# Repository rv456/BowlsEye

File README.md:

# Bowls Eye
-----------

Repository for team 18's Real Time Embedded Programming Raspberry Pi project.

Watch our promotional video at the link below!

# Installation
----------------

To install the bowls eye system on the Raspberry Pi run the following

    git clone https://github.com/rv456/BowlsEye.git
    cd BowlsEye/Code/Pi_BowlsEyeMain/
    make
    ./main
    
## Dependancies

The BowlsEye system requies Bluez and pigpio libraries.  It also requires that SPI and bluethooth are enabled on the Raspberry Pi

### Bluetooth 
    sudo apt-get install bluetooth blueman bluez libbluetooth-dev

### PIGPIO

    rm pigpio.tar
    sudo rm -rf PIGPIO
    wget abyz.me.uk/rpi/pigpio/pigpio.tar
    tar xf pigpio.tar
    cd PIGPIO
    make
    sudo make install
    
from the installation instructions [here](http://abyz.me.uk/rpi/pigpio/download.html)

### SPI

    sudo raspi-config

navigate to SPI and enable, you will then need to reboot the Pi to enable the changes

    sudo reboot

---------------------

## Repository Structure

[Code](https://github.com/rv456/BowlsEye/tree/master/Code) contains all of the code written for the Raspberry Pi and the external GUI.  Code documentation can be found [here](https://rv456.github.io/BowlsEye/).

[KiCad](https://github.com/rv456/BowlsEye/tree/master/KiCad) contains the various hardware design files used throught the project, including a full [BOM](https://github.com/rv456/BowlsEye/blob/master/KiCad/Shield/Fabrication/BOM/BOMfull.csv) and fabrication files. (note that part numbers for everything used in the project can also be found directly in the [schematics](https://github.com/rv456/BowlsEye/blob/master/KiCad/Shield) thanks to [kifields](http://kifield.readthedocs.io/en/latest/).

[Planner](https://github.com/rv456/BowlsEye/tree/master/Planner) contains documents related to project planning.  These will be removed once the project is completed.

[Resources](https://github.com/rv456/BowlsEye/tree/master/Resources) contains various datasheets, notes and other supporting files.

-----------

## Team Structure

[Harvey Leicester](https://github.com/rv456): Raspberry Pi programming and hardware design.

[Calum West](https://github.com/CalumWest): GUI programming and ultrasound guru.

# Problem
----------

Assistive technology is used throughout many sports to aid referees to determine the correct decision, or allow competitors to appeal against said decisions.  However, in the sport of lawn bowls, there is still a large factor of human error that can occur when measuring the distance between the jack and the bowls when the game is close.  As this is currently done with standard measurement techniques, any misreading of this distance by the referee will determine the wrong outcome of the game.  Therefore, this project aims to remove the possibility of human error in these measurements by designing a real time embedded system that can perform these measurments more accurately than a human.

# Solution
-----------

We have designed a system which uses ultrasonic transducers mounted on a stepper motor in order to map the distance from the jack to the surrounding area. This data is read via SPI by a Raspberry Pi and then transmitted via Bluetooth for a display on a GUI. More information can be found on our [wiki](https://github.com/rv456/BowlsEye/wiki).

A system overview is shown below, and you can follow our progress via this git, or our [facebook](https://www.facebook.com/Bowls-Eye-102409543919161/) or [twitter](https://twitter.com/bowlseyepi).

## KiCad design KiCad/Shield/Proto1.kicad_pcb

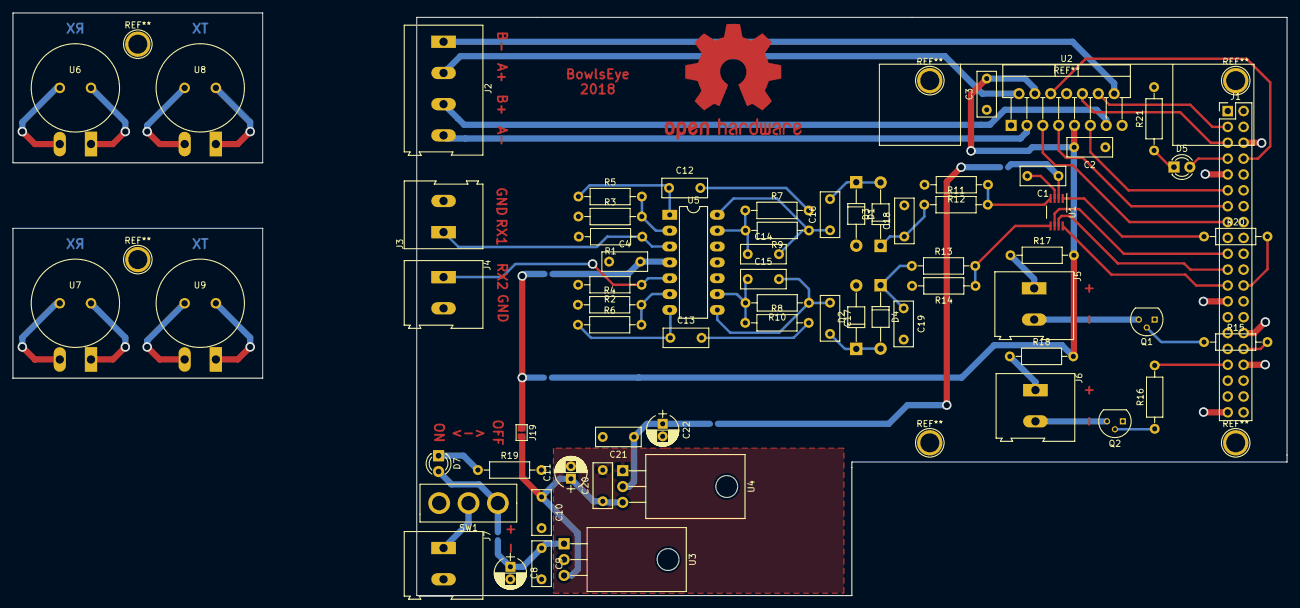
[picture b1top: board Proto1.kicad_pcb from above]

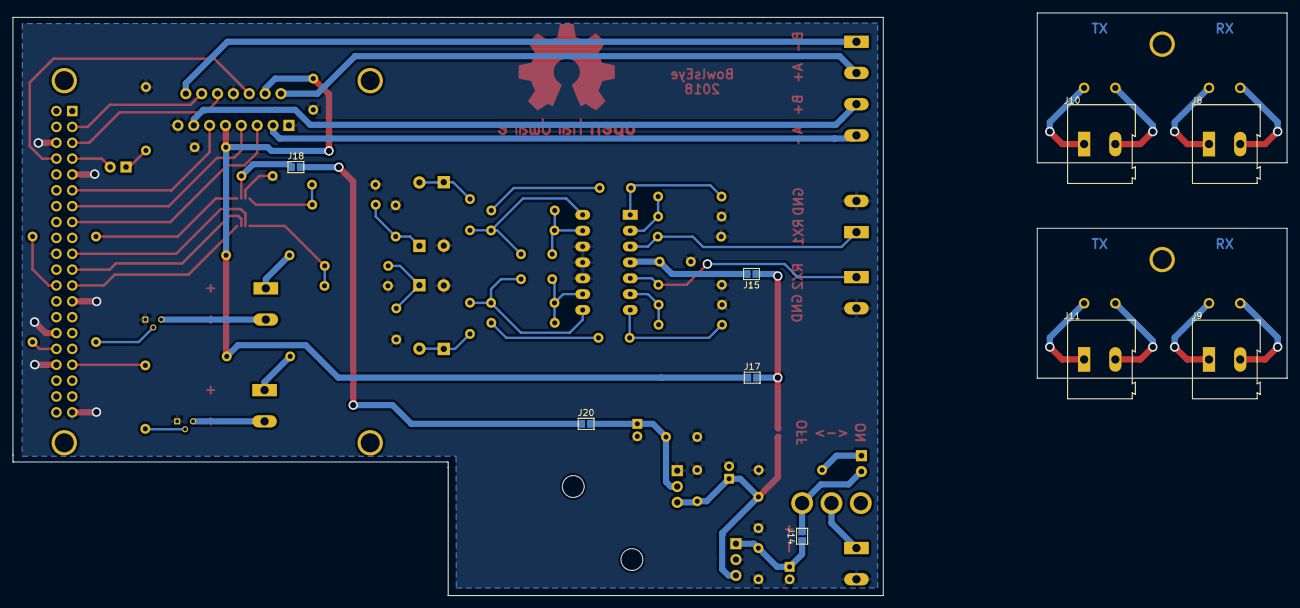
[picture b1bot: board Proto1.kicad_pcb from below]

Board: 2 copper layers, 204.1 x 93.3 mm, 75 parts (9 on the bottom side), 52 nets.

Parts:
C1, C2, C3, C4, C9, C10, C20, C21: 100nF; C_Rect_L7.2mm_W3.0mm_P5.00mm_FKS2_FKP2_MKS2_MKP2
C8, C11, C22: 10uF; CP_Radial_D5.0mm_P2.00mm
C12, C13: 10nF; C_Rect_L7.2mm_W3.0mm_P5.00mm_FKS2_FKP2_MKS2_MKP2
C14, C15: 10pF; C_Rect_L7.2mm_W3.0mm_P5.00mm_FKS2_FKP2_MKS2_MKP2
C16, C17, C18, C19: 1nF; C_Rect_L7.2mm_W3.0mm_P5.00mm_FKS2_FKP2_MKS2_MKP2
D1, D2, D3, D4: D; D_T-1_P10.16mm_Horizontal
D5, D7: LED; LED_D3.0mm
J1: CONN_02X20; Pin_Header_Straight_2x20_Pitch2.54mm
J2: CONN_01X04; TerminalBlock_Altech_AK300-4_P5.00mm
J3, J4, J5, J6, J7, J8, J9, J10, J11: CONN_01X02; TerminalBlock_Altech_AK300-2_P5.00mm
J14, J15, J17, J18, J19, J20: GS2
Q1, Q2: 2N3904; TO-92_Molded_Narrow
R1, R2: 3K9; R_Axial_DIN0207_L6.3mm_D2.5mm_P10.16mm_Horizontal
R3, R4, R7, R8: 1K; R_Axial_DIN0207_L6.3mm_D2.5mm_P10.16mm_Horizontal
R5, R6, R9, R10: 100K; R_Axial_DIN0207_L6.3mm_D2.5mm_P10.16mm_Horizontal
R11, R12, R13, R14, R15, R16, R17, R18, R19, R21: R; R_Axial_DIN0207_L6.3mm_D2.5mm_P10.16mm_Horizontal
R20: 0R; R_Axial_DIN0207_L6.3mm_D2.5mm_P10.16mm_Horizontal
SW1: SW_SPDT; SPDT
U1: ADC122S101; MyVSSOP-8_3.0x3.0mm_Pitch0.65mm
U2: L298_TH; TO-220-15_Vertical_StaggeredType1
U3: L78S05CV; TO-220-3_Horizontal
U4: LD1117S33TR_SOT223; TO-220-3_Horizontal
U5: LM324N; DIP-14_W7.62mm_LongPads
U6, U7, U8, U9: transducer

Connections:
+3V3: C1.1, C21.1, C22.1, J18.1, J18.2, J20.1, J20.2, U1.2, U4.2
+5V: C2.2, C3.2, C4.2, C10.1, C11.1, C20.1, J15.1, J15.2, J17.1, J17.2, J19.1, J19.2, R17.2, R18.2, U2.4, U2.9, U3.3, U4.3, U5.4
+Vs: C8.1, C9.1, D7.2, J14.1, J14.2, SW1.3, U3.1
DEBUG_PIN: D5.2, J1.7
GNDD: C1.2, C2.1, C3.1, C4.1, C8.2, C9.2, C10.2, C11.2, C18.2, C19.2, C20.2, C21.2, C22.2, D1.2, D2.2, J1.6, J1.9, J1.20, J1.25, J1.30, J1.34, J1.39, J3.2, J4.2, J7.2, J8.2, J9.2, Q1.1, Q2.1, R1.2, R2.2, R3.1, R4.1, R12.2, R14.2, R19.2, R21.2, U1.3, U2.1, U2.8, U2.15, U3.2, U4.1, U5.10, U5.11, U5.12, U6.2, U7.2
MOTOR_1_1: J1.15, U2.5
MOTOR_1_2: J1.13, U2.7
MOTOR_2_1: J1.5, U2.10
MOTOR_2_2: J1.3, U2.12
MOTOR_ENA: J1.8, U2.6
MOTOR_ENB: J1.11, U2.11
unnamed: C12.1, R5.1, U5.1
unnamed: C12.2, R7.2
unnamed: C13.1, R6.1, U5.7
unnamed: C13.2, R8.2
unnamed: C14.1, R7.1, R9.2, U5.13
unnamed: C14.2, C16.1, R9.1, U5.14
unnamed: C15.1, R8.1, R10.2, U5.9
unnamed: C15.2, C17.1, R10.1, U5.8
unnamed: C16.2, D1.1, D3.2
unnamed: C17.2, D2.1, D4.2
unnamed: C18.1, D3.1, R11.1
unnamed: C19.1, D4.1, R13.1
unnamed: D5.1, R21.1
unnamed: D7.1, R19.1
unnamed: J5.1, R17.1
unnamed: J5.2, Q1.3
unnamed: J6.1, R18.1
unnamed: J6.2, Q2.3
unnamed: J7.1, SW1.2
unnamed: J10.1, U8.1
unnamed: J10.2, U8.2
unnamed: J11.1, U9.1
unnamed: J11.2, U9.2
unnamed: Q1.2, R15.1
unnamed: Q2.2, R16.1
unnamed: R3.2, R5.2, U5.2
unnamed: R4.2, R6.2, U5.6
PHASE_A: J2.2, U2.2
PHASE_A-: J2.4, U2.3
PHASE_B: J2.3, U2.13
PHASE_B-: J2.1, U2.14
SPI_MISO: J1.21, U1.7
SPI_MOSI: J1.19, U1.6
SPI_NSS0: J1.24, R20.1, R20.2, U1.1
SPI_SCK: J1.23, U1.8
ULTRA_RX1: R11.2, R12.1, U1.4
ULTRA_RX1_RAW: J3.1, J8.1, R1.1, U5.3, U6.1
ULTRA_RX2: R13.2, R14.1, U1.5
ULTRA_RX2_RAW: J4.1, J9.1, R2.1, U5.5, U7.1
ULTRA_TX1: J1.32, R15.2
ULTRA_TX2: J1.33, R16.2

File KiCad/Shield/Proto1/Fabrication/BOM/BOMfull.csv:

Reference, Quantity, Value, Footprint, Datasheet, part#, rs#
C10 C20 C21 ,3,100nF,Capacitors_THT:C_Rect_L7.2mm_W3.0mm_P5.00mm_FKS2_FKP2_MKS2_MKP2,,,
C11 C22 ,2,10uF,Capacitors_THT:CP_Radial_D5.0mm_P2.00mm,,,
C12 C13 ,2,10nF,Capacitors_THT:C_Rect_L7.2mm_W3.0mm_P5.00mm_FKS2_FKP2_MKS2_MKP2,,UofG,
C14 C15 ,2,10pF,Capacitors_THT:C_Rect_L7.2mm_W3.0mm_P5.00mm_FKS2_FKP2_MKS2_MKP2,,UofG,
C16 C17 C18 C19 ,4,1nF,Capacitors_THT:C_Rect_L7.2mm_W3.0mm_P5.00mm_FKS2_FKP2_MKS2_MKP2,,UofG,
C8 ,1,10uF,Capacitors_THT:CP_Radial_D5.0mm_P2.00mm,,UofG,
C1 C2 C3 C4 C9 ,5,100nF,Capacitors_THT:C_Rect_L7.2mm_W3.0mm_P5.00mm_FKS2_FKP2_MKS2_MKP2,,UofG,
D1 D2 D3 D4 ,4,D,Diodes_THT:D_T-1_P10.16mm_Horizontal,,UofG,
D5 D7 ,2,LED,LEDs:LED_D3.0mm,,UofG,
J1 ,1,CONN_02X20,Pin_Headers:Pin_Header_Straight_2x20_Pitch2.54mm,,UofG,
J14 J15 J17 J18 J19 J20 ,6,GS2,Connectors:GS2,,,
J2 ,1,CONN_01X04,Connectors_Terminal_Blocks:TerminalBlock_Altech_AK300-4_P5.00mm,,UofG,
J10 J11 J3 J4 J5 J6 J7 J8 J9 ,9,CONN_01X02,Connectors_Terminal_Blocks:TerminalBlock_Altech_AK300-2_P5.00mm,,UofG,
Q1 Q2 ,2,BFY51,TO_SOT_Packages_THT:TO-92_Molded_Narrow,,UofG,
R1 R2 ,2,3K9,Resistors_THT:R_Axial_DIN0207_L6.3mm_D2.5mm_P10.16mm_Horizontal,,UofG,
R11 R12 R13 R14 R15 R16 R17 R18 R19 R21 ,10,R,Resistors_THT:R_Axial_DIN0207_L6.3mm_D2.5mm_P10.16mm_Horizontal,,UofG,
R20 ,1,0R,Resistors_THT:R_Axial_DIN0207_L6.3mm_D2.5mm_P10.16mm_Horizontal,,UofG,
R3 R4 R7 R8 ,4,1K,Resistors_THT:R_Axial_DIN0207_L6.3mm_D2.5mm_P10.16mm_Horizontal,,UofG,
R10 R5 R6 R9 ,4,100K,Resistors_THT:R_Axial_DIN0207_L6.3mm_D2.5mm_P10.16mm_Horizontal,,UofG,
SW1 ,1,SW_SPDT,BowlsEye:SPDT,,UofG,
U1 ,1,ADC122S101,BowlsEye:MyVSSOP-8_3.0x3.0mm_Pitch0.65mm,,ADC122S101CIMM/NOPB ,651-2278
U2 ,1,L298_TH,TO_SOT_Packages_THT:TO-220-15_Vertical_StaggeredType1,,UofG,
U3 ,1,L78S05CV,TO_SOT_Packages_THT:TO-220-3_Horizontal,,UofG,
U4 ,1,LD1117S33TR_SOT223,TO_SOT_Packages_THT:TO-220-3_Horizontal,,UofG,
U5 ,1,LM324N,Housings_DIP:DIP-14_W7.62mm_LongPads,,UofG,
U6 U7 ,2,transducer_r,BowlsEye:transducer,,MA40S4R ,237-0783
U8 U9 ,2,transducer_t,BowlsEye:transducer,,MA40S4S,237-0799

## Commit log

2018-01-24 Added transducer application note
2018-01-24 Added Motor data sheet
2018-01-24 Removed spaces from file name
2018-01-24 Started Planner proj and added more resources
2018-01-31 Added ADC breakout board
2018-02-06 Pushing from Pi
2018-02-07 Added gpio test
2018-02-07 Added pdf of ADCBreakout board
2018-02-07 Added to do list
2018-02-08 Added thread test Does hello world blinking on new thread
2018-02-08 Added pinout/mapping for Rpi GPIO connector
2018-02-08 Added some stepper motor resources
2018-02-12 Added some more resources
2018-02-12 Started SPI testing
2018-02-12 More spi testing
2018-02-13 Started updating README
2018-02-13 Added new readme
2018-02-13 Added block diagram
2018-02-13 Added cover photo
2018-02-13 Readme updated
2018-02-13 Added presentation for 13/2/18
2018-02-13 Updated presentation
2018-03-13 Added GUI testing code
2018-03-13 Added WIP proto1 schematic
2018-03-13 Added PWM demo
2018-03-13 clean up
2018-03-13 Added updated widget for drawing circle
2018-03-13 Added stepper motor code
2018-03-14 Updated GUI scripts
2018-03-14 improved stepper motor code
2018-03-14 Added scaleable circle widget
2018-03-14 updated schematic
2018-03-14 Added extra gui tests for plotting data points
2018-03-14 Added main GUI script
2018-03-15 removed hello world
2018-03-15 added PCB and PDF of schematics
2018-03-19 updated PCB and added fab files/bom
2018-03-19 Added bluetooth gui test
2018-03-20 changed socket port for gui
2018-03-20 added pi bluetooth code
2018-03-22 added doc folder
2018-03-22 added html folder
2018-03-22 Initial commit to gh-pages branch
2018-03-22 cleaned up gh-pages branch
2018-03-22 added some doxygen stuff
2018-03-22 another attept at adding doxygen...
2018-03-22 added .nojeckyll file
2018-03-22 more tests
2018-03-22 removed everything
2018-03-22 initial docs commit
2018-03-24 added more documentation
2018-03-24 Create README.md
    [Here] (https://rv456.github.io/BowlsEye/) is the documentation for the code of the project
2018-03-25 minor readme change
2018-03-25 added readme for all code sub directories
2018-03-25 added transducer code
2018-03-25 updated documentation
2018-03-25 more documentation
2018-04-02 added bluetooth control over stepper motor
2018-04-06 added adc test code
2018-04-08 Auto stash before merge of "master" and "origin/master"
2018-04-08 Added proto2 kicad files
2018-04-08 Added pdfs of proto2
2018-04-09 Finished proto2 board
2018-04-10 Added pulse signal code
2018-04-11 Added test file for pwm and spi
2018-04-11 added scope traces of ultrasound experiments
2018-04-12 Added updated GUI code
2018-04-14 added proto code
2018-04-15 updated pi code
2018-04-15 added updated gui
2018-04-15 minor gui changes
2018-04-15 Updated GUI main
2018-04-15 added updated pi
2018-04-15 added clearing graphic to gui
2018-04-15 added software block diagram
2018-04-15 updated software diagram
2018-04-15 more updates to software diagram
2018-04-15 new rapsberry pi code
2018-04-15 more pi updating
2018-04-15 safety commit
2018-04-15 added proto2 pdfs
2018-04-15 added pngs of pcbs
2018-04-15 Added display functionality
2018-04-16 cleaned up gui folder
2018-04-16 added cad files
2018-04-16 Pi code repo cleanup
2018-04-16 updated doxygen
2018-04-16 added install info to readme
